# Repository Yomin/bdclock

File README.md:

# Bulbdial Clock Board

Board for the bulbdial clock developed at
[Evil Mad Scientist Laboratories](http://www.evilmadscientist.com/2009/a-bulbdial-clock/).
Due to current availability of only attiny45's the multiplexing is partly outsourced with
one 7bit binary counter and two 8bit addressable latches.

For synchronization the board is equipped with a socket for a pollin DCF77 module (810 054).

## License

MIT

## Parts

count|name|info
---|---|---|---
1x|attiny 25/45/85|
1x|HEF4024B|7 bit binary counter
1x|HCF4724B|8 bit addressable latch
2x|BC547B|
1x|red diffuse led|
1x|4pin socket|
1x|10pin isp socket|
1x|powerjack|
1x|2pin clamp|power
1x|3pin clamp|led gnd
1x|12pin clamp|led vcc
2x|1N4004|
1x|300nF|
1x|100nF|
1x|1uF pol|
1x|7805|
6x|10k|
1x|1k|
4x|250|
1x|pollin dcf77 module|
36x|white point leds|for the actual clock

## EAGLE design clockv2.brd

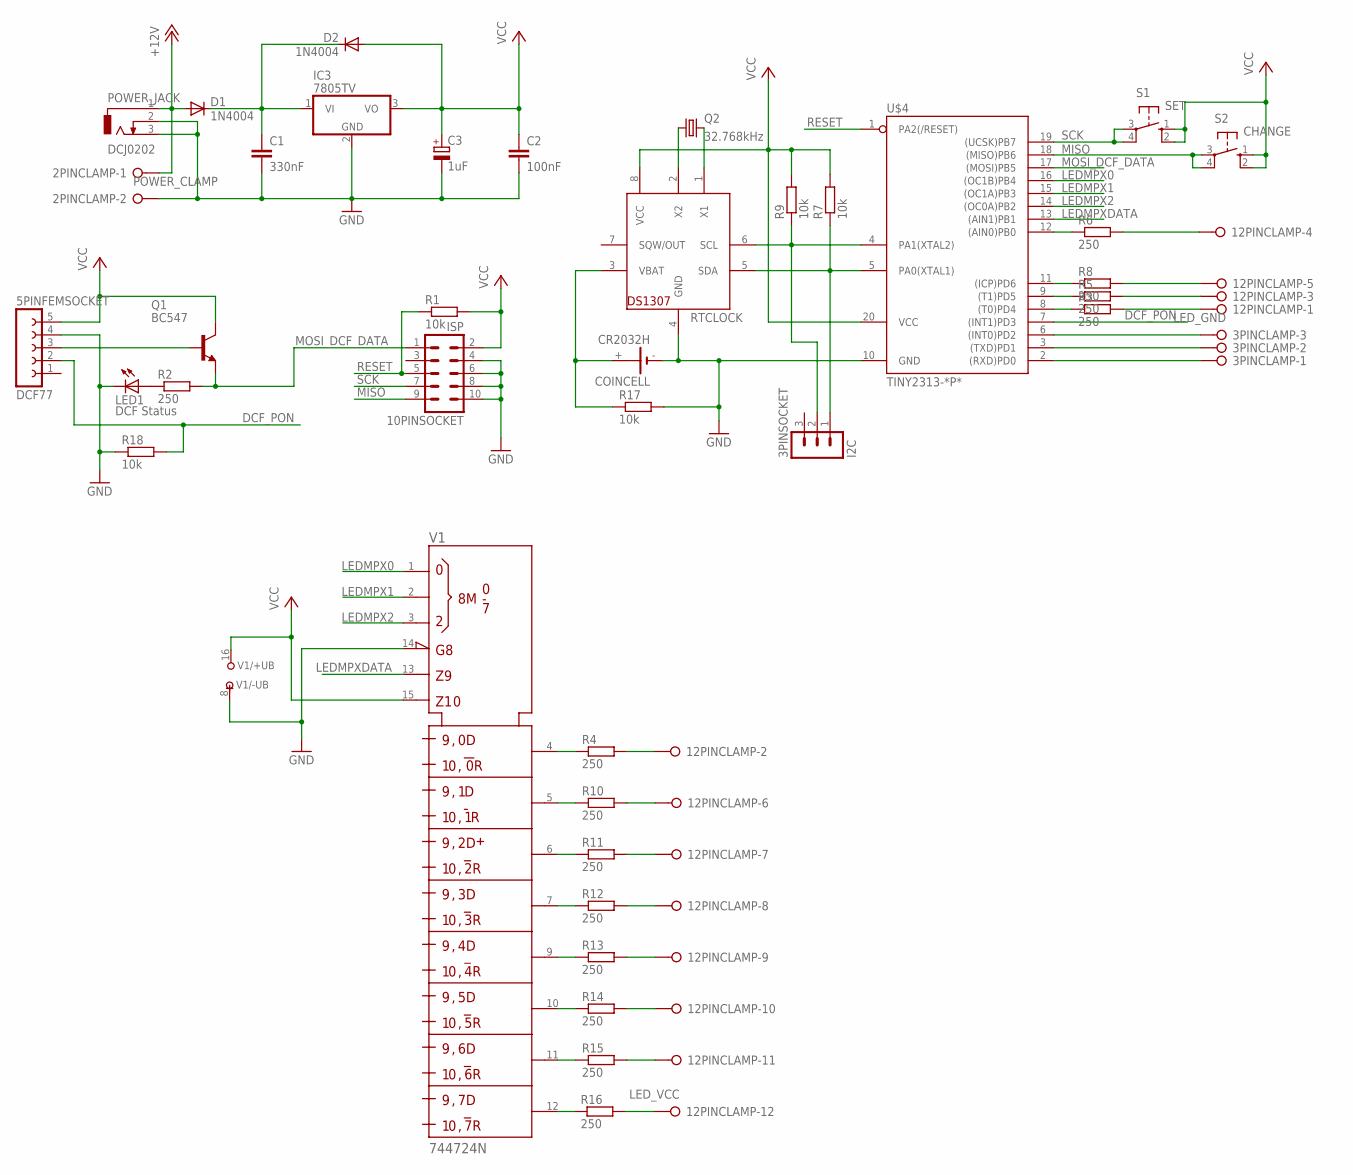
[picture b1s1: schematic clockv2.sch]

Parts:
2PINCLAMP: POWER_CLAMP; W237-132
3PINCLAMP: LED_GND; W237-133
3PINSOCKET: I2C; MA03-1
5PINFEMSOCKET: DCF77; FE05-1
10PINSOCKET: ISP; ML10
12PINCLAMP: LED_VCC; W237-12P
C1: 330nF; C050-025X075
C2: 100nF; C050-025X075
C3: 1uF; E2-4
COINCELL: CR2032H
D1, D2: 1N4004; DO41-10
IC3: 7805TV; TO220V
LED1: DCF Status; LED5MM
POWER_JACK: DCJ0202
Q1: BC547; TO92
Q2: 32.768kHz; TC38H
R1, R7, R9, R17, R18: 10k; 0204/5
R2, R3, R4, R5, R6, R8, R10, R11, R12, R13, R14, R15, R16: 250; 0204/5
RTCLOCK: DS1307; DIL08
S1: SET; B3F-10XX
S2: CHANGE; B3F-10XX
U$4: TINY2313-*P*; DIL20
V1: 744724N; DIL16

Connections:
+12V: 2PINCLAMP.1, D1.A, POWER_JACK.1
DCF_PON: 5PINFEMSOCKET.2, R18.2, U$4.7 ((INT1)PD3)
GND: 2PINCLAMP.2, 5PINFEMSOCKET.4, 10PINSOCKET.4, 10PINSOCKET.6, 10PINSOCKET.8, 10PINSOCKET.10, C1.2, C2.2, C3.-, COINCELL.-, IC3.2 (GND), LED1.K (C), POWER_JACK.2, POWER_JACK.3, R17.2, R18.1, RTCLOCK.4 (GND), U$4.10 (GND), V1.8 (-UB), V1.14 (!G)
LEDMPX0: U$4.16 ((OC1B)PB4), V1.1 (S0)
LEDMPX1: U$4.15 ((OC1A)PB3), V1.2 (S1)
LEDMPX2: U$4.14 ((OC0A)PB2), V1.3 (S2)
LEDMPXDATA: U$4.13 ((AIN1)PB1), V1.13 (D)
MISO: 10PINSOCKET.9, S2.3, S2.4 (P1), U$4.18 ((MISO)PB6)
MOSI_DCF_DATA: 10PINSOCKET.1, Q1.1 (E), R2.2, U$4.17 ((MOSI)PB5)
unnamed: 12PINCLAMP.4, R6.2
unnamed: 12PINCLAMP.2, R4.2
unnamed: 12PINCLAMP.3, R5.2
unnamed: 5PINFEMSOCKET.3, Q1.2 (B)
unnamed: 12PINCLAMP.1, R3.2
unnamed: 12PINCLAMP.5, R8.2
unnamed: 12PINCLAMP.6, R10.2
unnamed: R5.1, U$4.9 ((T1)PD5)
unnamed: R10.1, V1.5 (Q1)
unnamed: 12PINCLAMP.9, R13.2
unnamed: 12PINCLAMP.10, R14.2
unnamed: 12PINCLAMP.11, R15.2
unnamed: 12PINCLAMP.12, R16.2
unnamed: R3.1, U$4.8 ((T0)PD4)
unnamed: R4.1, V1.4 (Q0)
unnamed: LED1.A, R2.1
unnamed: C1.1, D1.C, D2.C, IC3.1 (VI)
unnamed: R6.1, U$4.12 ((AIN0)PB0)
unnamed: R8.1, U$4.11 ((ICP)PD6)
unnamed: 12PINCLAMP.8, R12.2
unnamed: 12PINCLAMP.7, R11.2
unnamed: R11.1, V1.6 (Q2)
unnamed: R12.1, V1.7 (Q3)
unnamed: R16.1, V1.12 (Q7)
unnamed: R13.1, V1.9 (Q4)
unnamed: R14.1, V1.10 (Q5)
unnamed: R15.1, V1.11 (Q6)
unnamed: 3PINCLAMP.3, U$4.6 ((INT0)PD2)
unnamed: 3PINCLAMP.2, U$4.3 ((TXD)PD1)
unnamed: 3PINCLAMP.1, U$4.2 ((RXD)PD0)
unnamed: 3PINSOCKET.2, R9.1, RTCLOCK.6 (SCL), U$4.4 (PA1(XTAL2))
unnamed: 3PINSOCKET.1, R7.1, RTCLOCK.5 (SDA), U$4.5 (PA0(XTAL1))
unnamed: COINCELL.+, R17.1, RTCLOCK.3 (VBAT)
unnamed: Q2.1, RTCLOCK.2 (X2)
unnamed: Q2.2, RTCLOCK.1 (X1)
RESET: 10PINSOCKET.5, R1.1, U$4.1 (PA2(/RESET))
SCK: 10PINSOCKET.7, S1.3, S1.4 (P1), U$4.19 ((UCSK)PB7)
VCC: 5PINFEMSOCKET.5, 10PINSOCKET.2, C2.1, C3.+, D2.A, IC3.3 (VO), Q1.3 (C), R1.2, R7.2, R9.2, RTCLOCK.8 (VCC), S1.1 (S), S1.2 (S1), S2.1 (S), S2.2 (S1), U$4.20 (VCC), V1.15 (CLR), V1.16 (+UB)

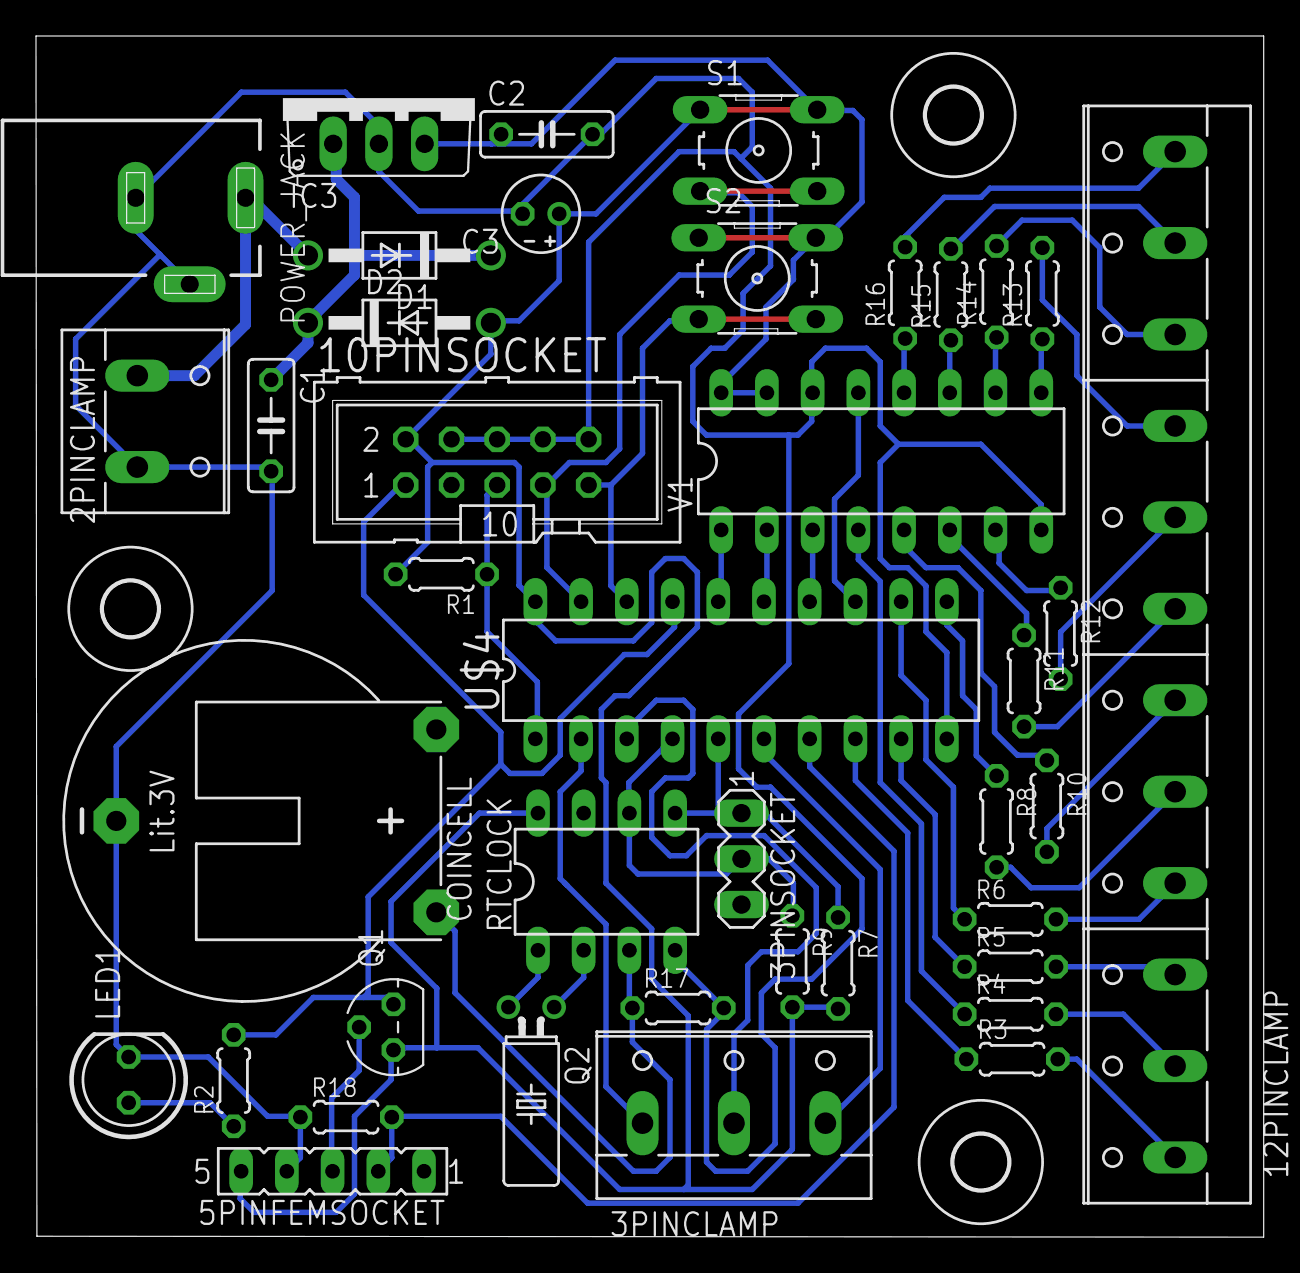
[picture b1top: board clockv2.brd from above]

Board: 2 copper layers, 68.2 x 66.7 mm, 43 parts (0 on the bottom side), 47 nets.

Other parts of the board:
U$1, U$2, U$3: 3,0

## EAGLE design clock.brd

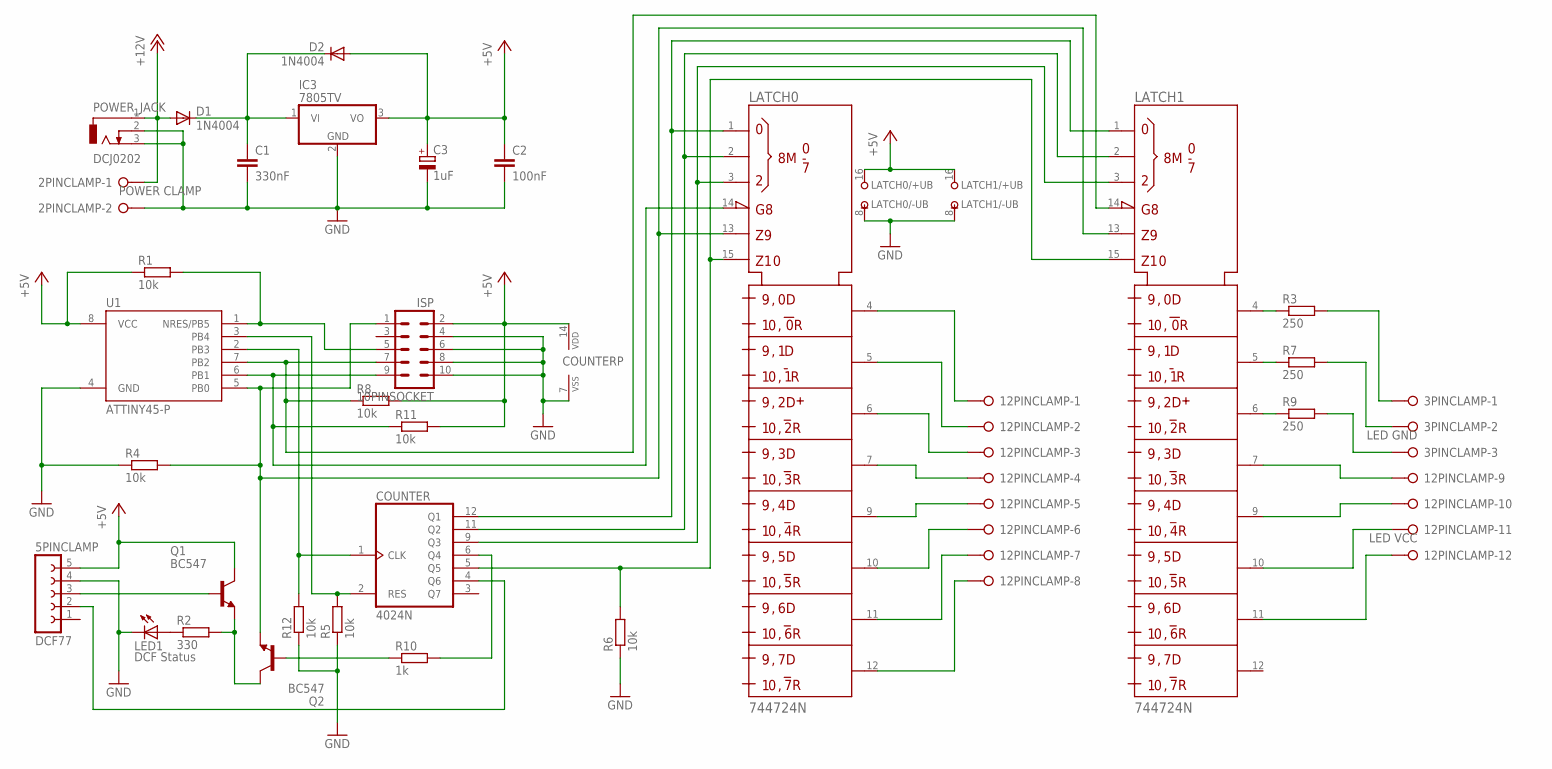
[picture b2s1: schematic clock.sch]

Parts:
2PINCLAMP: POWER CLAMP; W237-132
3PINCLAMP: LED GND; W237-3E
5PINCLAMP: DCF77; FE05-1
10PINSOCKET: ISP; ML10
12PINCLAMP: LED VCC; W237-12P
C1: 330nF; C050-025X075
C2: 100nF; C050-025X075
C3: 1uF; E2-4
COUNTER: 4024N; DIL14
D1, D2: 1N4004; DO41-10
IC3: 7805TV; TO220V
LATCH0, LATCH1: 744724N; DIL16
LED1: DCF Status; LED5MM
POWER_JACK: DCJ0202
Q1, Q2: BC547; TO92
R1, R4, R5, R6, R8, R11, R12: 10k; 0204/5
R2: 330; 0204/5
R3, R7, R9: 250; 0204/5
R10: 1k; 0204/5
U1: ATTINY45-P; PDIP08_300MIL

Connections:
+5V: 5PINCLAMP.5, 10PINSOCKET.2, C2.1, C3.+, COUNTER.14 (VDD), D2.A, IC3.3 (VO), LATCH0.16 (+UB), LATCH1.16 (+UB), Q1.3 (C), R1.1, R8.2, R11.2, U1.8 (VCC)
+12V: 2PINCLAMP.1, D1.A, POWER_JACK.1
CLOCK: COUNTER.1 (CLK), R12.2, U1.2 (PB3)
DATA: 10PINSOCKET.1, LATCH0.13 (D), LATCH1.13 (D), Q2.1 (E), R4.2, U1.5 (PB0)
DCF_DATA: 5PINCLAMP.3, Q1.2 (B)
DCF_PON: 5PINCLAMP.2, COUNTER.4 (Q6)
GND: 2PINCLAMP.2, 5PINCLAMP.4, 10PINSOCKET.4, 10PINSOCKET.6, 10PINSOCKET.8, 10PINSOCKET.10, C1.2, C2.2, C3.-, COUNTER.7 (VSS), IC3.2 (GND), LATCH0.8 (-UB), LATCH1.8 (-UB), LED1.K (C), POWER_JACK.2, POWER_JACK.3, R4.1, R5.1, R6.1, R12.1, U1.4 (GND)
LATCH0: 10PINSOCKET.7, LATCH1.14 (!G), R8.1, U1.7 (PB2)
LATCH1: 10PINSOCKET.9, LATCH0.14 (!G), R11.1, U1.6 (PB1)
unnamed: 12PINCLAMP.1, LATCH0.4 (Q0)
unnamed: 12PINCLAMP.6, LATCH0.10 (Q5)
unnamed: 12PINCLAMP.2, LATCH0.5 (Q1)
unnamed: 12PINCLAMP.8, LATCH0.12 (Q7)
unnamed: 12PINCLAMP.7, LATCH0.11 (Q6)
unnamed: 12PINCLAMP.5, LATCH0.9 (Q4)
unnamed: 12PINCLAMP.4, LATCH0.7 (Q3)
unnamed: 12PINCLAMP.3, LATCH0.6 (Q2)
unnamed: 3PINCLAMP.2, R7.2
unnamed: 3PINCLAMP.3, R9.2
unnamed: 12PINCLAMP.9, LATCH1.7 (Q3)
unnamed: LATCH1.4 (Q0), R3.1
unnamed: 12PINCLAMP.11, LATCH1.10 (Q5)
unnamed: 12PINCLAMP.12, LATCH1.11 (Q6)
unnamed: LED1.A, R2.1
unnamed: C1.1, D1.C, D2.C, IC3.1 (VI)
unnamed: Q1.1 (E), Q2.3 (C), R2.2
unnamed: LATCH1.6 (Q2), R9.1
unnamed: COUNTER.6 (Q4), R10.2
unnamed: LATCH1.5 (Q1), R7.1
unnamed: COUNTER.5 (Q5), LATCH0.15 (CLR), LATCH1.15 (CLR), R6.2
unnamed: 10PINSOCKET.5, R1.2, U1.1 (NRES/PB5)
unnamed: COUNTER.12 (Q1), LATCH0.1 (S0), LATCH1.1 (S0)
unnamed: Q2.2 (B), R10.1
unnamed: 3PINCLAMP.1, R3.2
unnamed: COUNTER.9 (Q3), LATCH0.3 (S2), LATCH1.3 (S2)
unnamed: COUNTER.11 (Q2), LATCH0.2 (S1), LATCH1.2 (S1)
unnamed: 12PINCLAMP.10, LATCH1.9 (Q4)
RESET: COUNTER.2 (RES), R5.2, U1.3 (PB4)

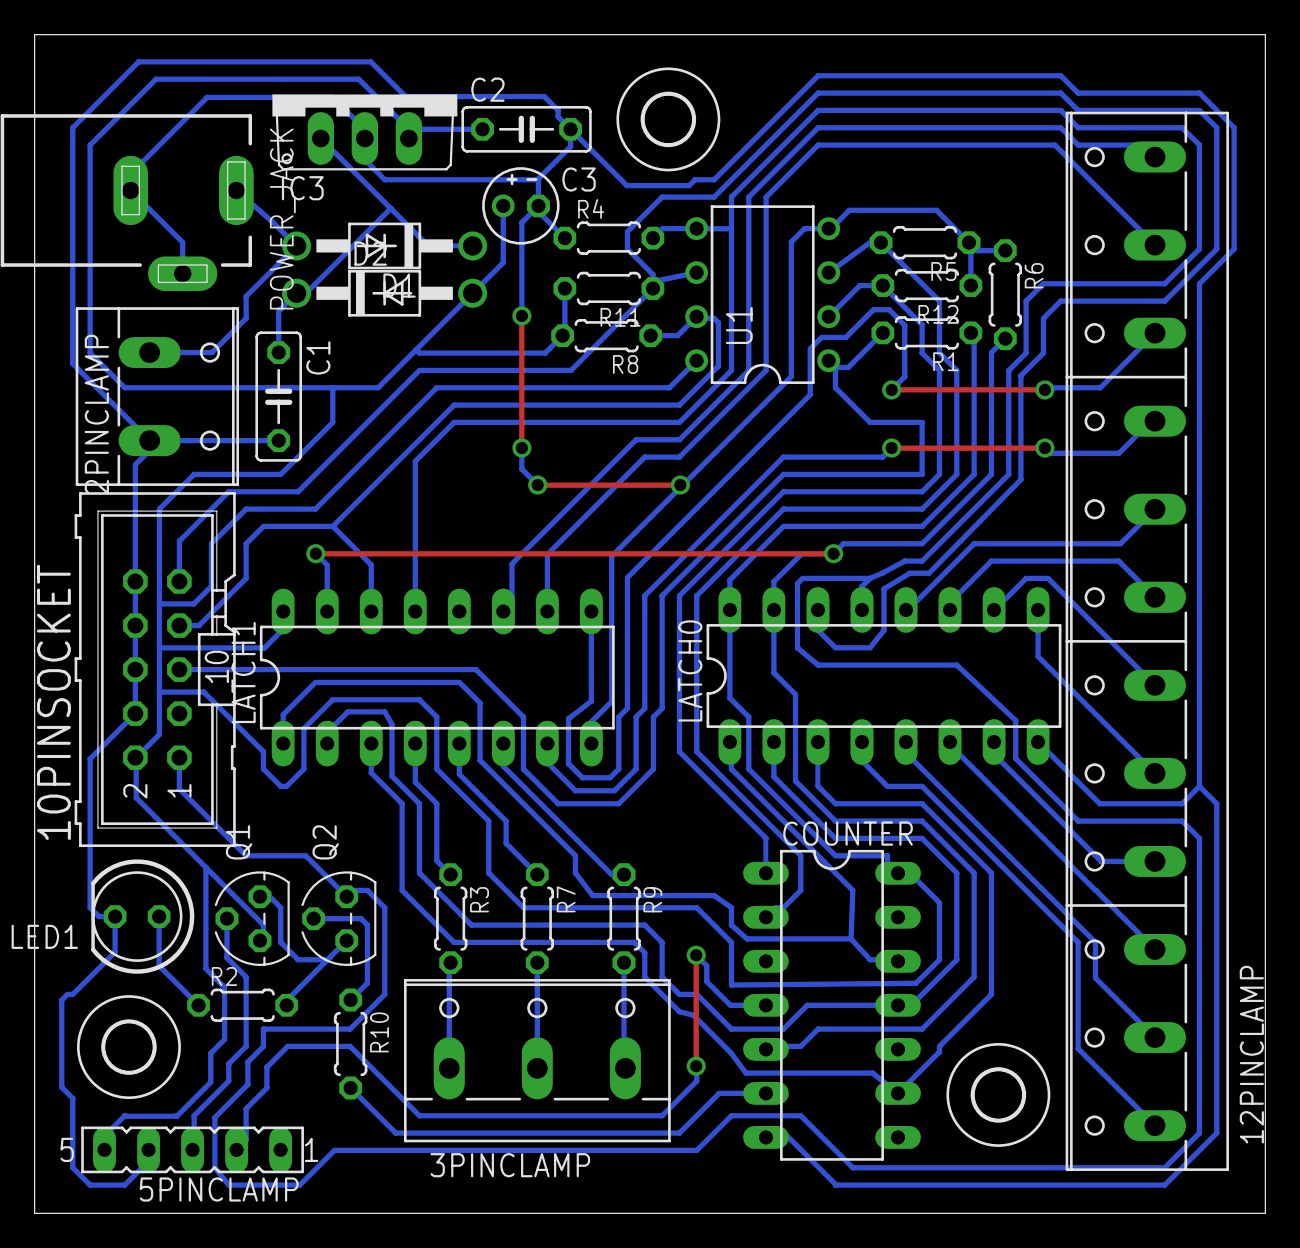
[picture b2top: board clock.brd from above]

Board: 2 copper layers, 71.0 x 68.0 mm, 34 parts (0 on the bottom side), 38 nets.

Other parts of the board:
U$1, U$2, U$3: 2,8

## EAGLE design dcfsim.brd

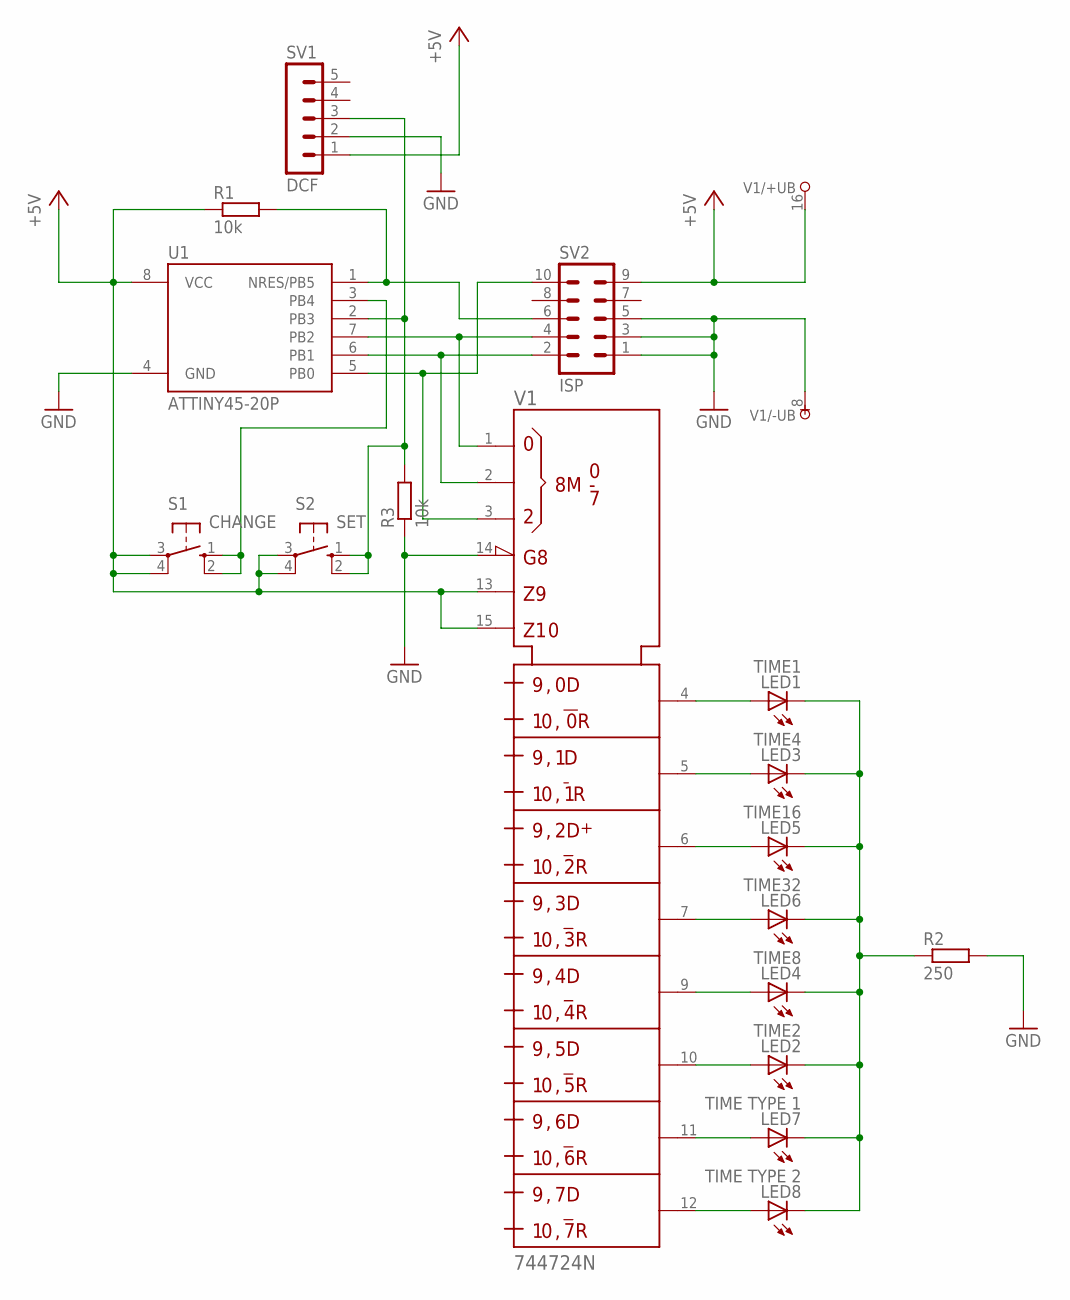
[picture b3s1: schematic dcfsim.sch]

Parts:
LED1: TIME1; LED5MM
LED2: TIME2; LED5MM
LED3: TIME4; LED5MM
LED4: TIME8; LED5MM
LED5: TIME16; LED5MM
LED6: TIME32; LED5MM
LED7: TIME TYPE 1; LED5MM
LED8: TIME TYPE 2; LED5MM
R1, R3: 10k; 0204/5
R2: 250; 0204/5
S1: CHANGE; B3F-10XX
S2: SET; B3F-10XX
SV1: DCF; MA05-1
SV2: ISP; ML10
U1: ATTINY45-20P; PDIP08_300MIL
V1: 744724N; DIL16

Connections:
+5V: R1.1, S1.3, S1.4 (P1), S2.3, S2.4 (P1), SV1.1, SV2.9, U1.8 (VCC), V1.13 (D), V1.15 (CLR), V1.16 (+UB)
GND: R2.2, R3.1, SV1.2, SV2.1, SV2.3, SV2.5, U1.4 (GND), V1.8 (-UB), V1.14 (!G)
unnamed: R1.2, SV2.6, U1.1 (NRES/PB5)
unnamed: SV2.4, U1.7 (PB2), V1.1 (S0)
unnamed: SV2.2, U1.6 (PB1), V1.2 (S1)
unnamed: SV2.10, U1.5 (PB0), V1.3 (S2)
unnamed: R3.2, S2.1 (S), S2.2 (S1), SV1.3, U1.2 (PB3)
unnamed: LED1.A, V1.4 (Q0)
unnamed: LED2.A, V1.10 (Q5)
unnamed: LED4.A, V1.9 (Q4)
unnamed: LED6.A, V1.7 (Q3)
unnamed: LED5.A, V1.6 (Q2)
unnamed: LED3.A, V1.5 (Q1)
unnamed: S1.1 (S), S1.2 (S1), U1.3 (PB4)
unnamed: LED7.A, V1.11 (Q6)
unnamed: LED8.A, V1.12 (Q7)
RROU: LED1.K (C), LED2.K (C), LED3.K (C), LED4.K (C), LED5.K (C), LED6.K (C), LED7.K (C), LED8.K (C), R2.1

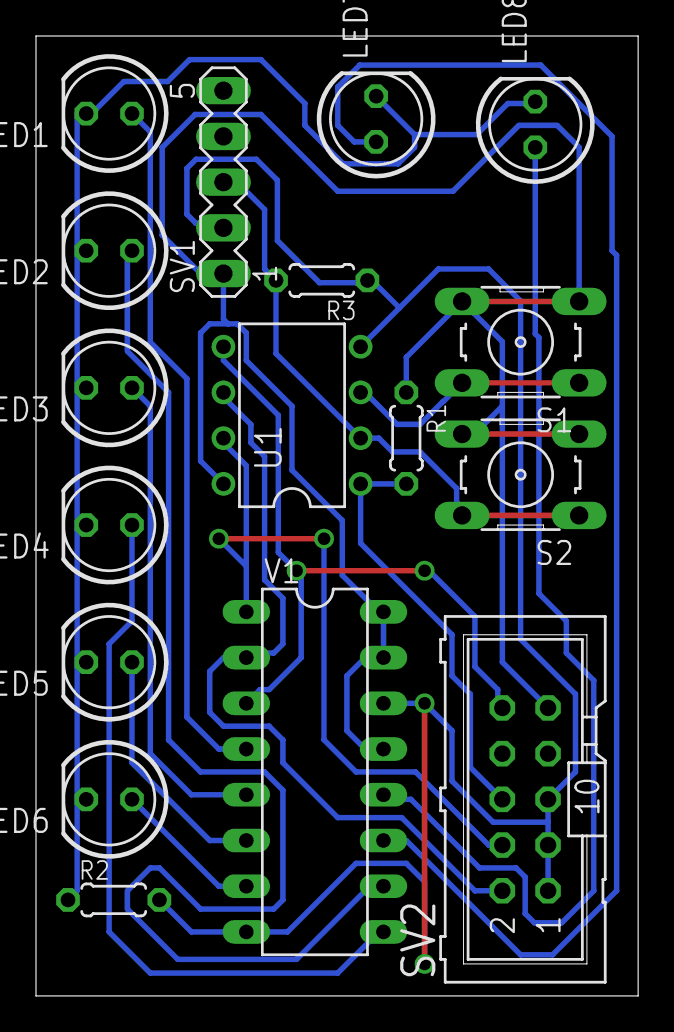
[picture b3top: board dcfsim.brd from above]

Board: 2 copper layers, 33.5 x 53.3 mm, 17 parts (0 on the bottom side), 17 nets.

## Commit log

2013-03-01 initial commit, schematic and board done
2013-03-01 update readme with dcf module
2013-03-02 update readme with partlist
2013-03-02 change powerjack to horizontal, fix DRC errors, mirror logos and text, add gnd plane, set wire width to 12mil
2013-03-03 fix ERC errors of schematic, add missing VCC/VSS pins of ICs, replace jumpers with vias
2013-03-03 add *.pro to gitignore
2013-03-03 add DCF simulator board
2013-03-04 rename clockset to dcfsim, move buttons upwards, move text to doc layer
2013-03-04 rotate isp 180°, connect 4th gnd pin, move logo/text to doc layer
2013-03-05 add restrict rect for oshw text
2013-03-06 add clock v2
